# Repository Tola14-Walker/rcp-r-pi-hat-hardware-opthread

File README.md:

# rcp-r-pi-hat-hardware-opthread
# rcp-r-pi-hat-hardware-opthread

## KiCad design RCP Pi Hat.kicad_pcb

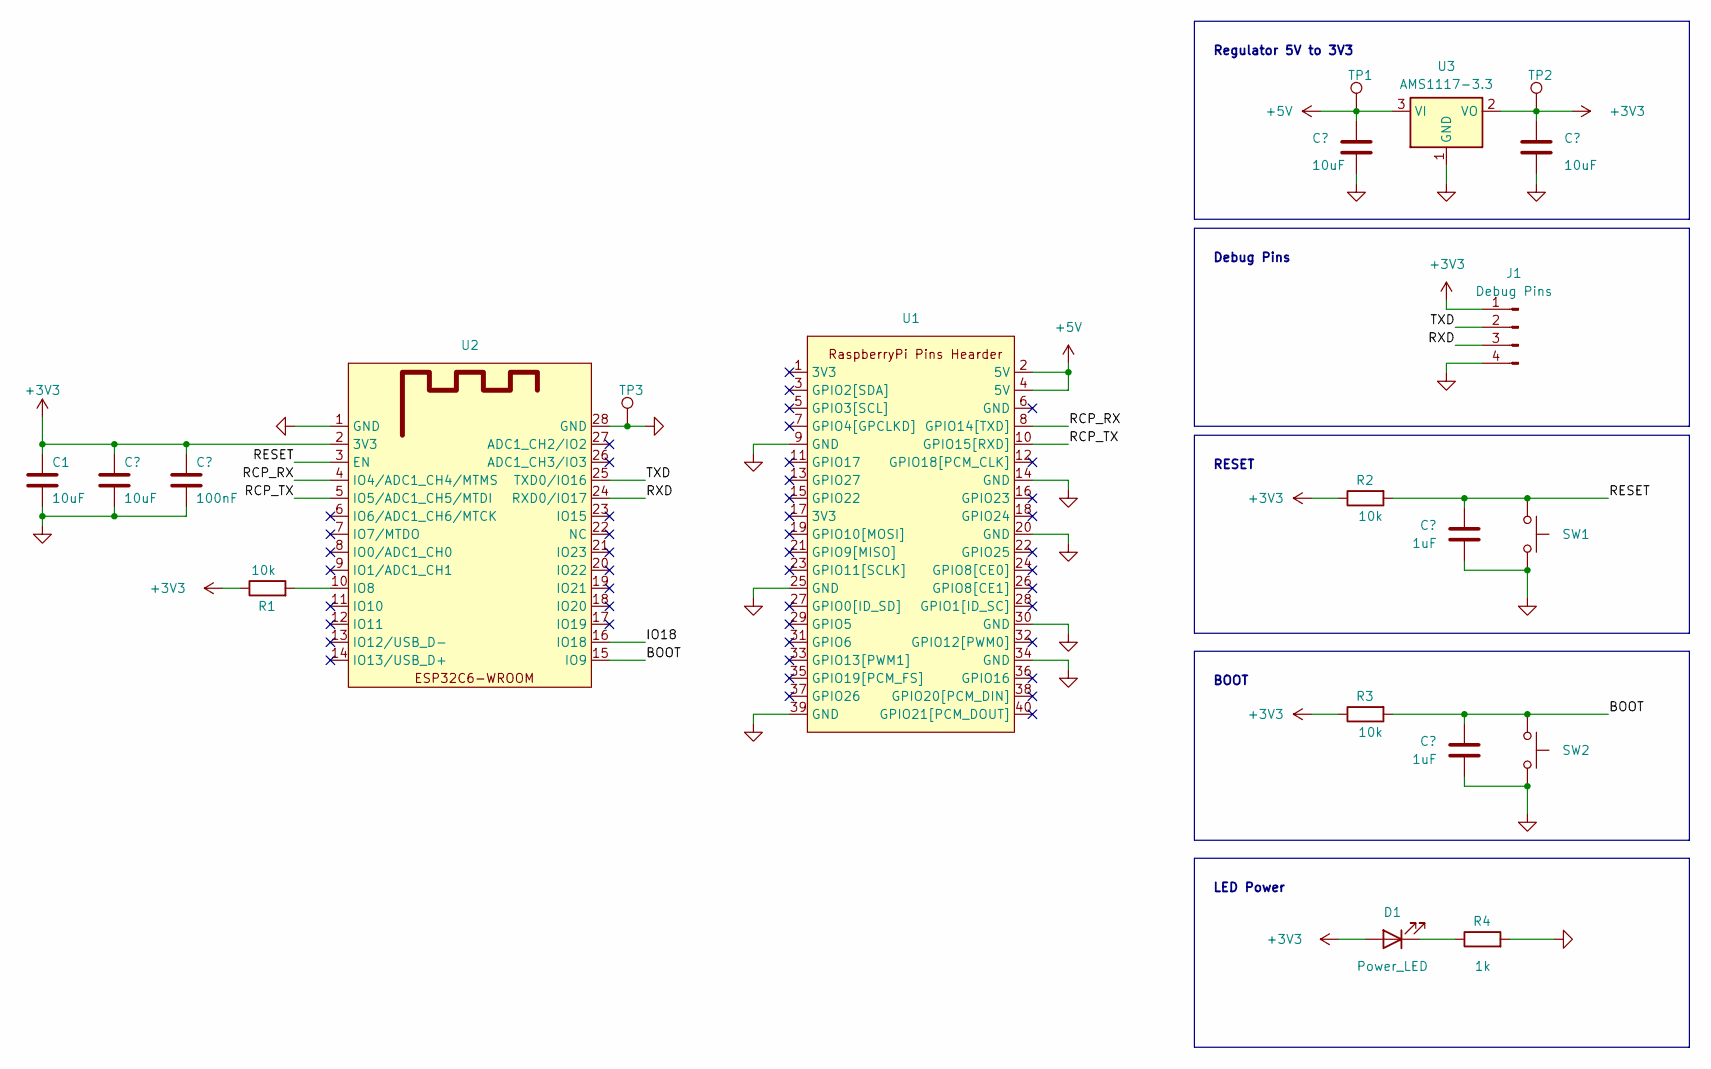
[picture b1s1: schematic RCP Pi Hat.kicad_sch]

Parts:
C1, C2: 10uF; C_0805_2012Metric; Part Number CL31A106KBHNNNE; LCSC C13585
C3: 100nF; C_0805_2012Metric; LCSC C14663
C4, C7: 10uF; C_0805_2012Metric; LCSC_Part C1713
C5, C6: 1uF; C_0805_2012Metric; LCSC C15849
D1: Power_LED; LED_0805_2012Metric; Part Number 19-213/Y2C-CQ2R2L/3T(CY); LCSC C72038
J1: Debug Pins; PinHeader_1x04_P2.54mm_Horizontal
R1, R2, R3: 10k; R_0805_2012Metric; Part Number 0603WAF1002T5E; LCSC C25804
R4: 1k; R_0805_2012Metric; Part Number 0603WAF1001T5E; LCSC C21190
SW1, SW2: SW_Push_6x6mm
TP1, TP2, TP3: TestPoint; TestPoint_Pad_D1.5mm
U1: RaspberryPiHeaderPin40
U2: ES32C6-WOOR_1U_footprint
U3: AMS1117-3.3; SOT-223-3_TabPin2

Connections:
+3V3: C1.1, C2.1, C3.1, C7.1, D1.2 (A), J1.1, R1.1, R2.1, R3.1, TP2.1, U2.2 (3V3), U3.2 (VO)
+5V: C4.1, TP1.1, U1.2 (5V), U1.4 (5V), U3.3 (VI)
/BOOT: C6.1, R3.2, SW2.2, U2.15 (IO9)
/IO18: U2.16 (IO18)
/RCP_RX: U1.8 (GPIO14[TXD]), U2.4 (IO4/ADC1_CH4/MTMS)
/RCP_TX: U1.10 (GPIO15[RXD]), U2.5 (IO5/ADC1_CH5/MTDI)
/RESET: C5.1, R2.2, SW1.2, U2.3 (EN)
/RXD: J1.3, U2.24 (RXD0/IO17)
/TXD: J1.2, U2.25 (TXD0/IO16)
GND: C1.2, C2.2, C3.2, C4.2, C5.2, C6.2, C7.2, J1.4, R4.2, SW1.1, SW2.1, TP3.1, U1.9 (GND), U1.14 (GND), U1.20 (GND), U1.25 (GND), U1.30 (GND), U1.34 (GND), U1.39 (GND), U2.1 (GND), U2.28 (GND), U3.1 (GND)
unnamed: D1.1 (K), R4.1
unnamed: R1.2, U2.10 (IO8)

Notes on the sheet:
Debug Pins
Regulator 5V to 3V3
LED Power
RESET
BOOT

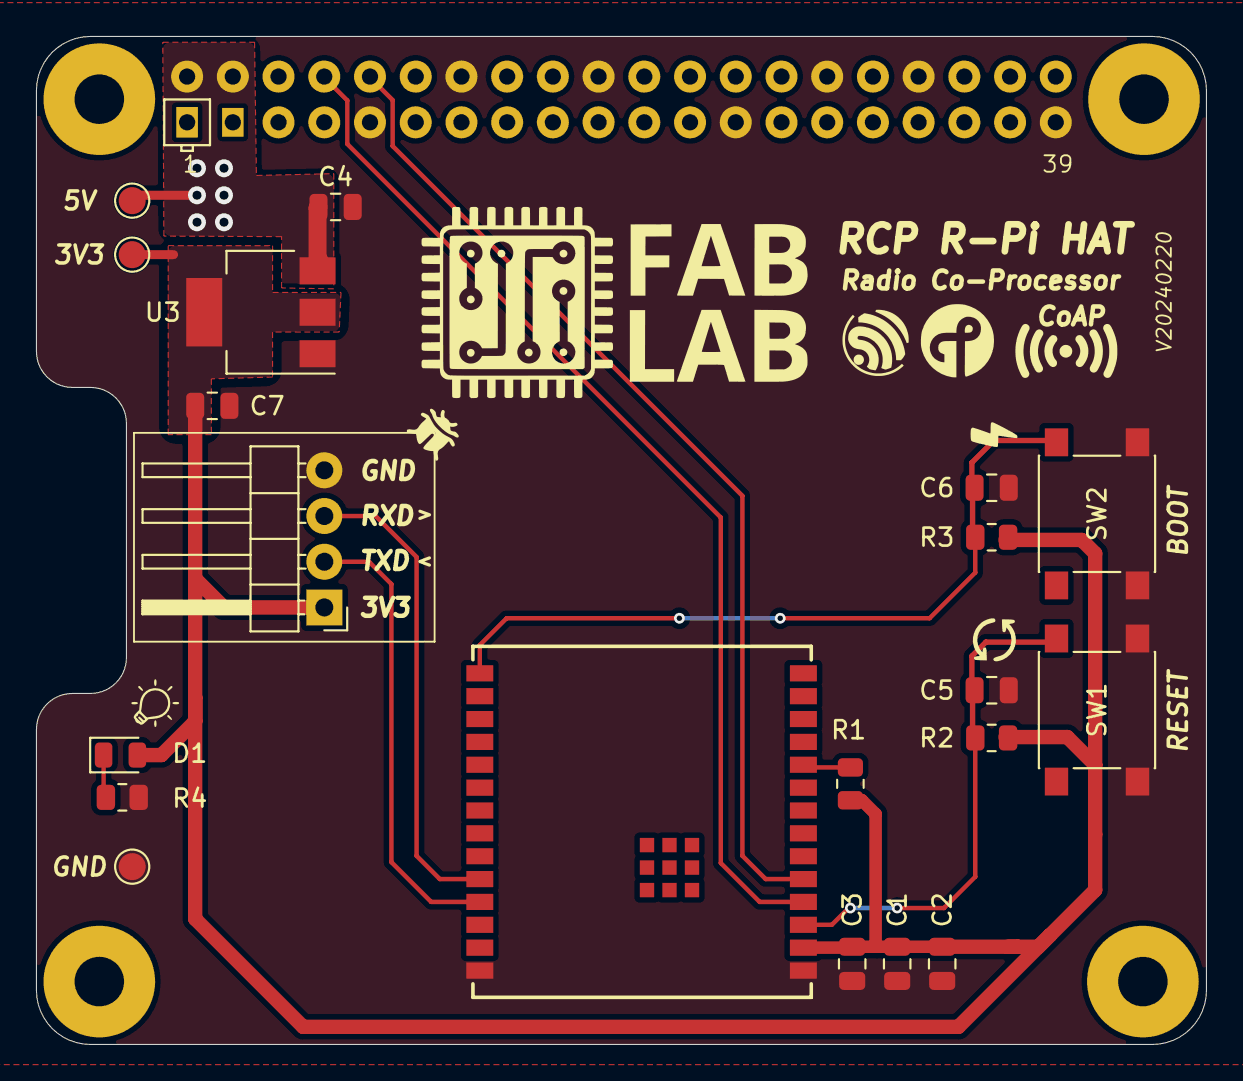
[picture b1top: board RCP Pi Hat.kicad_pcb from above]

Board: 2 copper layers, 65.0 x 56.0 mm, 21 parts (0 on the bottom side), 11 nets.

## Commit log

2024-02-18 v20240216
2024-02-20 V20240220
